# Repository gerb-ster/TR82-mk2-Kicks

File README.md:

# TR82 mk2 'Kicks'

Second version of the TR82 project; proper PCB's this time! I've combined the BassDrums and the SnareDrum to 
a single board. I've added a OpAmp buffer to the output and changed the output impedance to a more standard
1k. Next to that I've also added a Gate-to-Trigger circuit based on a design by Ken Stone. It converts the 
rising edge of a Gate signal into a short trigger pulse. By changin the level of the gate/trigger input you
can control how 'hard' you hit the drums. Higher levels means more 'accent'.

The Designs and Mods of the drum voices are the same as in the 'original' TR82.

There is a 'internal trigger' connection added to the mainboard of the PCB. This can be used to hook it up to
a seperate controller board. Maybe :). 

### Links

https://www.gerbster.nl/tr82/  
https://www.elby-designs.com/webtek/cgs/cgs24/cgs24_gatetotrigger.html

## Status: Work in Progress

- done: first schematic & board design
- done: breadboard and test
- done: design frontpanel
- todo: order PCB and build prototype

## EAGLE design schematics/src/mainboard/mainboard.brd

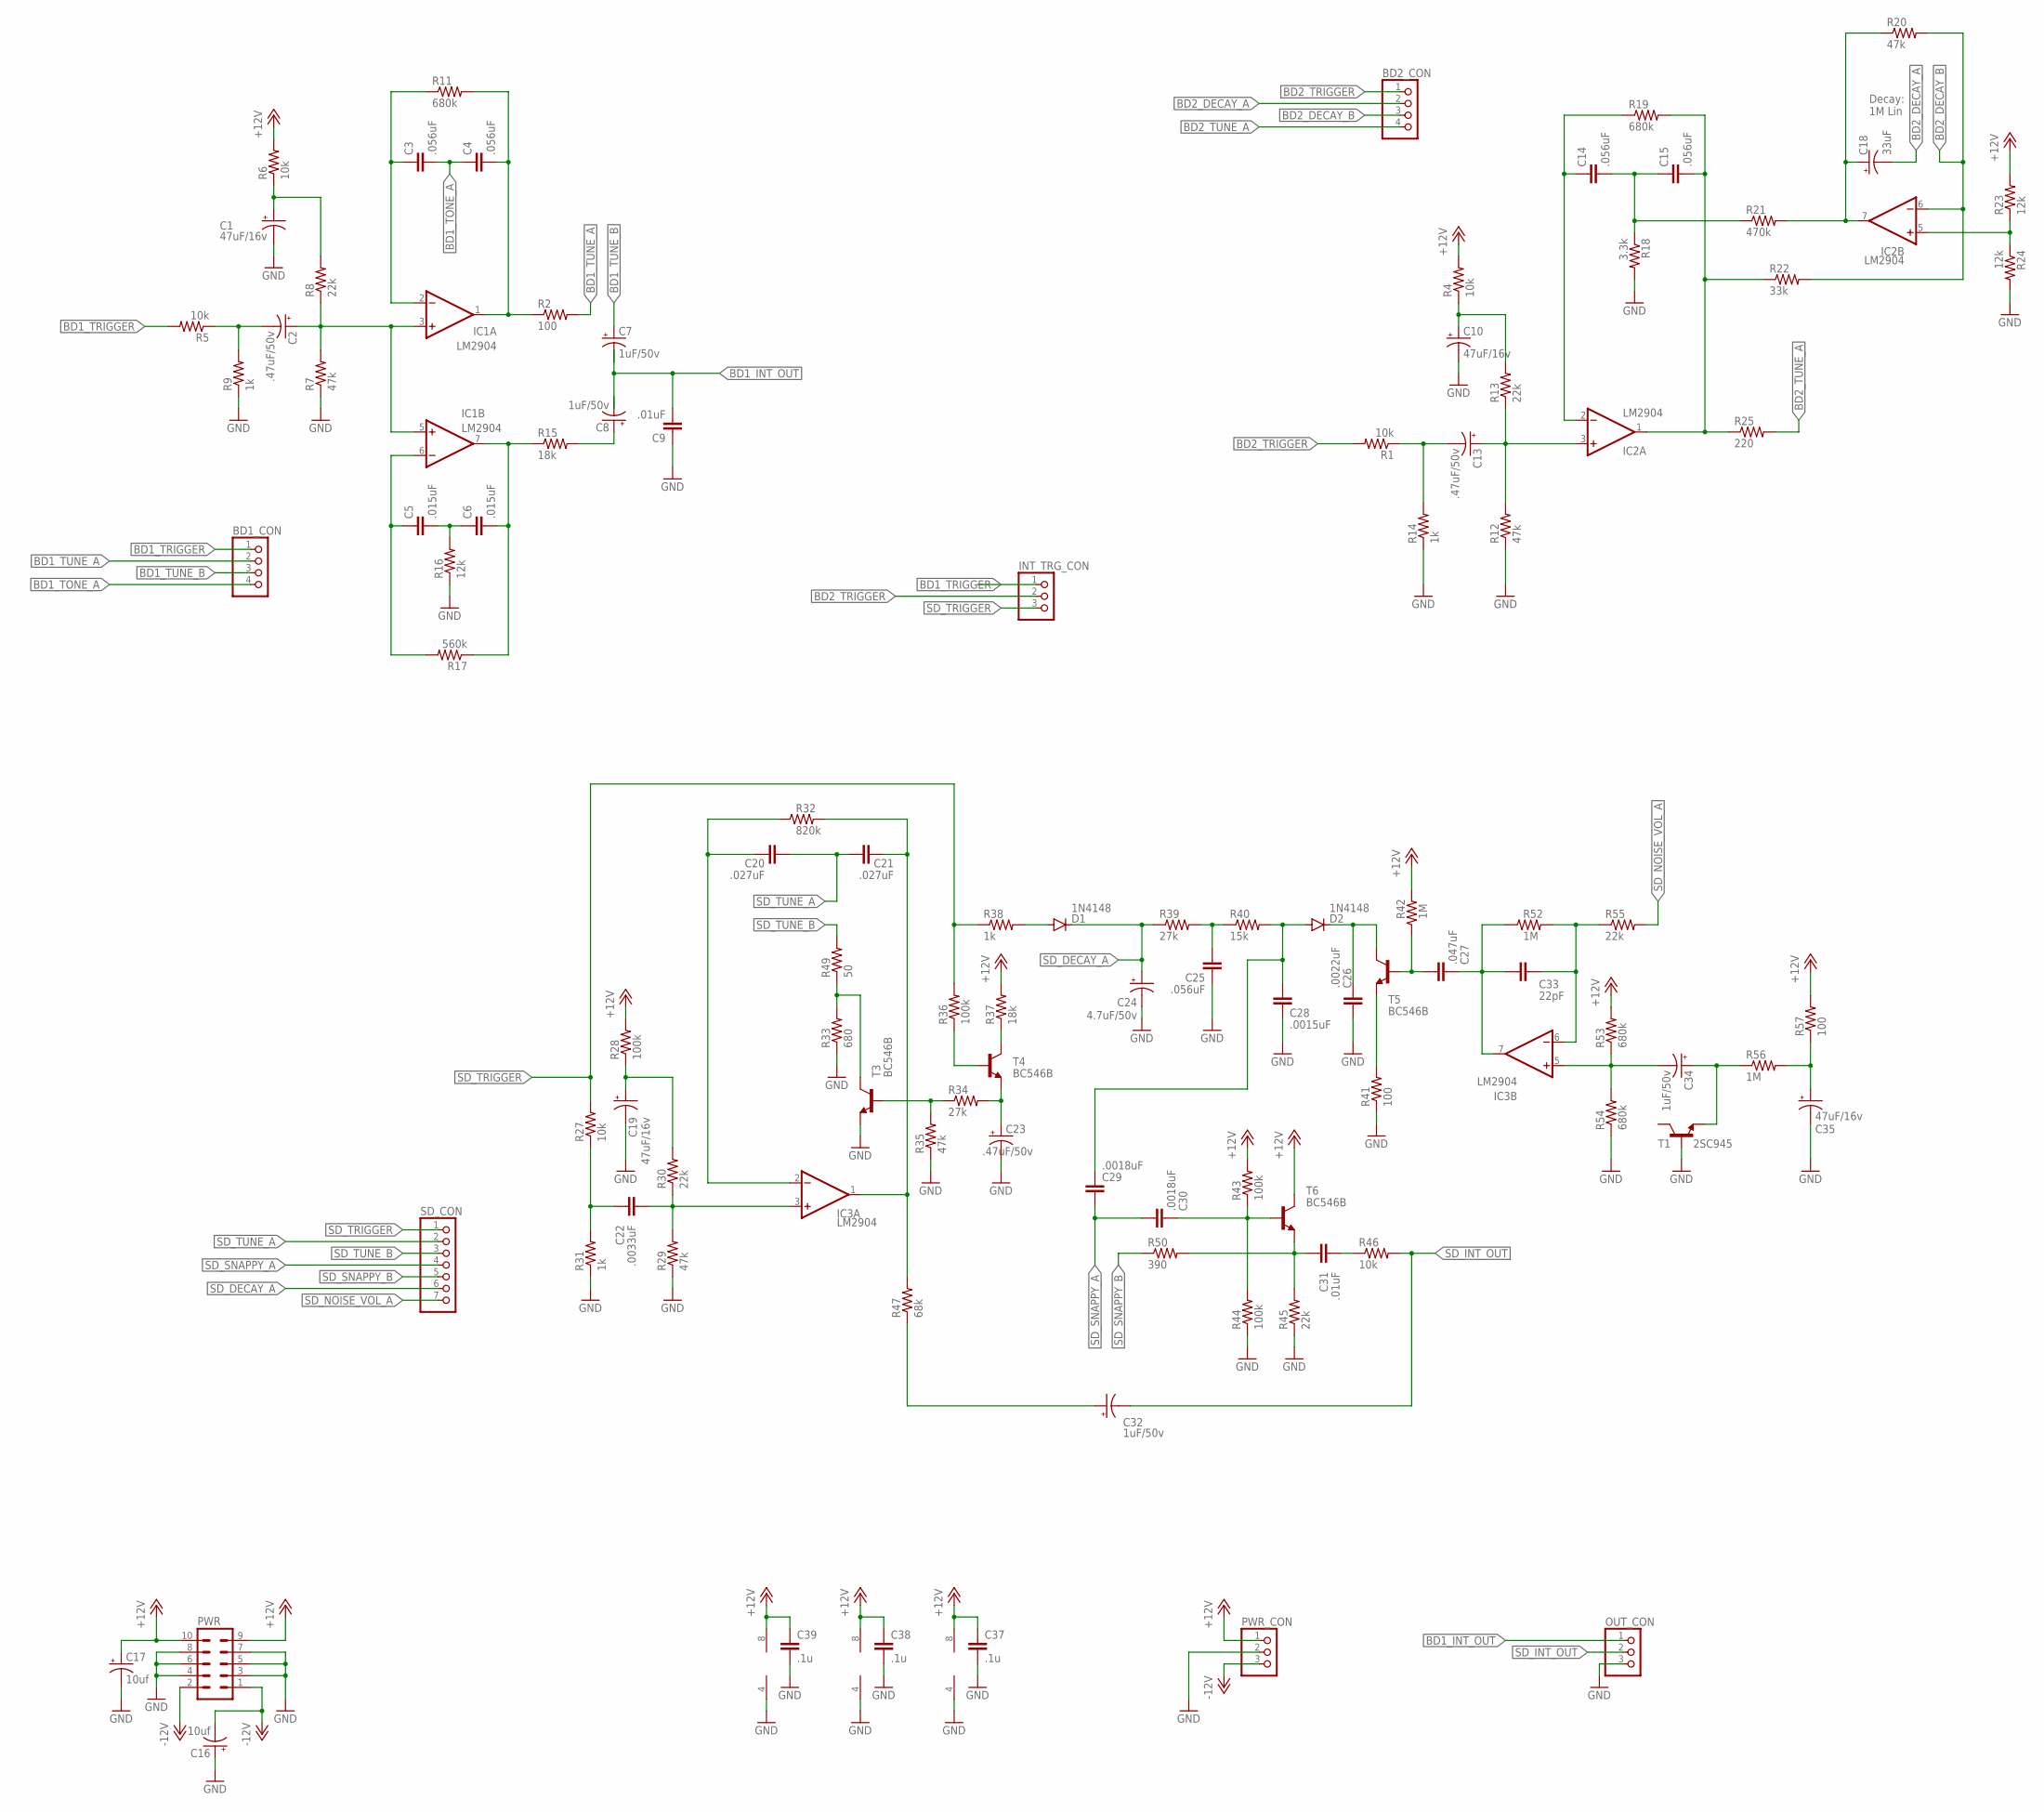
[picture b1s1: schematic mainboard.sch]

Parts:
BD1_CON, BD2_CON: PINHD-1X4; 1X04
C1, C35: 47uF/16v; E2,5-5
C2: .47uF/50v; E2,5-5
C3, C4, C14, C15, C25: .056uF; C050-024X044
C5, C6: .015uF; C050-024X044
C7, C8, C34: 1uF/50v; E2,5-5
C9, C31: .01uF; C050-024X044
C10, C19: 47uF/16v; E2,5-6
C13, C23: .47uF/50v; E2,5-6
C16, C17: 10uf; E2,5-5
C18: 33uF; E2,5-5
C20, C21: .027uF; C050-024X044
C22: .0033uF; C050-024X044
C24: 4.7uF/50v; E2,5-6
C26: .0022uF; C050-024X044
C27: .047uF; C050-024X044
C28: .0015uF; C050-024X044
C29, C30: .0018uF; C050-024X044
C32: 1uF/50v; E2,5-6
C33: 22pF; C050-024X044
C37, C38, C39: .1u; C050-024X044
D1, D2: 1N4148; DO35-7
IC1, IC2, IC3: LM2904; DIL08
INT_TRG_CON: PINHD-1X3; 1X03
OUT_CON: PINHD-1X3; 1X03
PWR: ML10
PWR_CON: PINHD-1X3; 1X03
R1, R4, R5, R6, R27, R46: 10k; 0207/7
R2, R41, R57: 100; 0207/7
R7, R12, R20, R29, R35: 47k; 0207/7
R8, R13, R30, R45, R55: 22k; 0207/7
R9, R14, R31, R38: 1k; 0207/7
R11, R19, R53, R54: 680k; 0207/7
R15, R37: 18k; 0207/7
R16, R23, R24: 12k; 0207/7
R17: 560k; 0207/7
R18: 3.3k; 0207/7
R21: 470k; 0207/7
R22: 33k; 0207/7
R25: 220; 0207/7
R28, R36, R43, R44: 100k; 0207/7
R32: 820k; 0207/2V
R33: 680; 0207/7
R34, R39: 27k; 0207/7
R40: 15k; 0207/7
R42, R52, R56: 1M; 0207/7
R47: 68k; 0207/7
R49: 50; 0207/7
R50: 390; 0207/7
SD_CON: PINHD-1X7; 1X07
T1: 2SC945; TO92-ECB
T3, T4, T5, T6: BC546B; TO92-CBE

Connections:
+12V: C17.+, C37.1, C38.1, C39.1, IC1.8 (V+), IC2.8 (V+), IC3.8 (V+), PWR.9, PWR.10, PWR_CON.1, R4.2, R6.2, R23.2, R28.2, R37.2, R42.2, R43.2, R53.2, R57.2, T6.C
-12V: C16.-, PWR.1, PWR.2, PWR_CON.3
BD1_INT_OUT: C7.-, C8.-, C9.2, OUT_CON.1
BD1_TONE_A: BD1_CON.4, C3.2, C4.1
BD1_TRIGGER: BD1_CON.1, INT_TRG_CON.1, R5.2
BD1_TUNE_A: BD1_CON.2, R2.2
BD1_TUNE_B: BD1_CON.3, C7.+
BD2_DECAY_A: BD2_CON.2, C18.-
BD2_DECAY_B: BD2_CON.3, IC2.6 (-IN), R20.2, R22.2
BD2_TRIGGER: BD2_CON.1, INT_TRG_CON.2, R1.2
BD2_TUNE_A: BD2_CON.4, R25.2
GND: C1.-, C9.1, C10.-, C16.+, C17.-, C19.-, C23.-, C24.-, C25.1, C26.1, C28.1, C35.-, C37.2, C38.2, C39.2, IC1.4 (V-), IC2.4 (V-), IC3.4 (V-), OUT_CON.3, PWR.3, PWR.4, PWR.5, PWR.6, PWR.7, PWR.8, PWR_CON.2, R7.1, R9.1, R12.1, R14.1, R16.1, R18.2, R24.2, R29.1, R31.1, R33.1, R35.1, R41.1, R44.1, R45.1, R54.1, T1.B, T3.E
unnamed: C13.-, R1.1, R14.2
unnamed: C2.-, R5.1, R9.2
unnamed: C2.+, IC1.3 (+IN), IC1.5 (+IN), R7.2, R8.1
unnamed: C1.+, R6.1, R8.2
unnamed: C5.2, C6.1, R16.2
unnamed: C3.1, IC1.2 (-IN), R11.1
unnamed: C13.+, IC2.3 (+IN), R12.2, R13.1
unnamed: C10.+, R4.1, R13.2
unnamed: C6.2, IC1.7 (OUT), R15.1, R17.1
unnamed: C5.1, IC1.6 (-IN), R17.2
unnamed: C4.2, IC1.1 (OUT), R2.1, R11.2
unnamed: C8.+, R15.2
unnamed: C14.1, IC2.2 (-IN), R19.1
unnamed: C14.2, C15.1, R18.1, R21.1
unnamed: C15.2, IC2.1 (OUT), R19.2, R22.1, R25.1
unnamed: C18.+, IC2.7 (OUT), R20.1, R21.2
unnamed: IC2.5 (+IN), R23.1, R24.1
unnamed: C22.1, R27.1, R31.2
unnamed: C22.2, IC3.3 (+IN), R29.2, R30.1
unnamed: C19.+, R28.1, R30.2
unnamed: C20.1, IC3.2 (-IN), R32.1
unnamed: C21.2, IC3.1 (OUT), R32.2, R47.2
unnamed: R33.2, R49.1, T3.C
unnamed: R34.1, R35.2, T3.B
unnamed: C23.+, R34.2, T4.E
unnamed: R36.1, T4.B
unnamed: R37.1, T4.C
unnamed: D1.A, R38.2
unnamed: C25.2, R39.2, R40.1
unnamed: C28.2, C29.1, D2.A, R40.2
unnamed: C26.2, D2.C, T5.C
unnamed: R41.2, T5.E
unnamed: C27.1, R42.1, T5.B
unnamed: C31.1, R45.2, R50.2, T6.E
unnamed: C31.2, R46.1
unnamed: C32.+, R47.1
unnamed: C30.2, R43.1, R44.2, T6.B
unnamed: C27.2, C33.1, IC3.7 (OUT), R52.1
unnamed: C33.2, IC3.6 (-IN), R52.2, R55.1
unnamed: C34.-, IC3.5 (+IN), R53.1, R54.2
unnamed: C34.+, R56.1, T1.E
unnamed: C35.+, R56.2, R57.1
SD_DECAY_A: C24.+, D1.C, R39.1, SD_CON.6
SD_INT_OUT: C32.-, OUT_CON.2, R46.2
SD_NOISE_VOL_A: R55.2, SD_CON.7
SD_SNAPPY_A: C29.2, C30.1, SD_CON.4
SD_SNAPPY_B: R50.1, SD_CON.5
SD_TRIGGER: INT_TRG_CON.3, R27.2, R36.2, R38.1, SD_CON.1
SD_TUNE_A: C20.2, C21.1, SD_CON.2
SD_TUNE_B: R49.2, SD_CON.3

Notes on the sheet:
Decay: 1M Lin

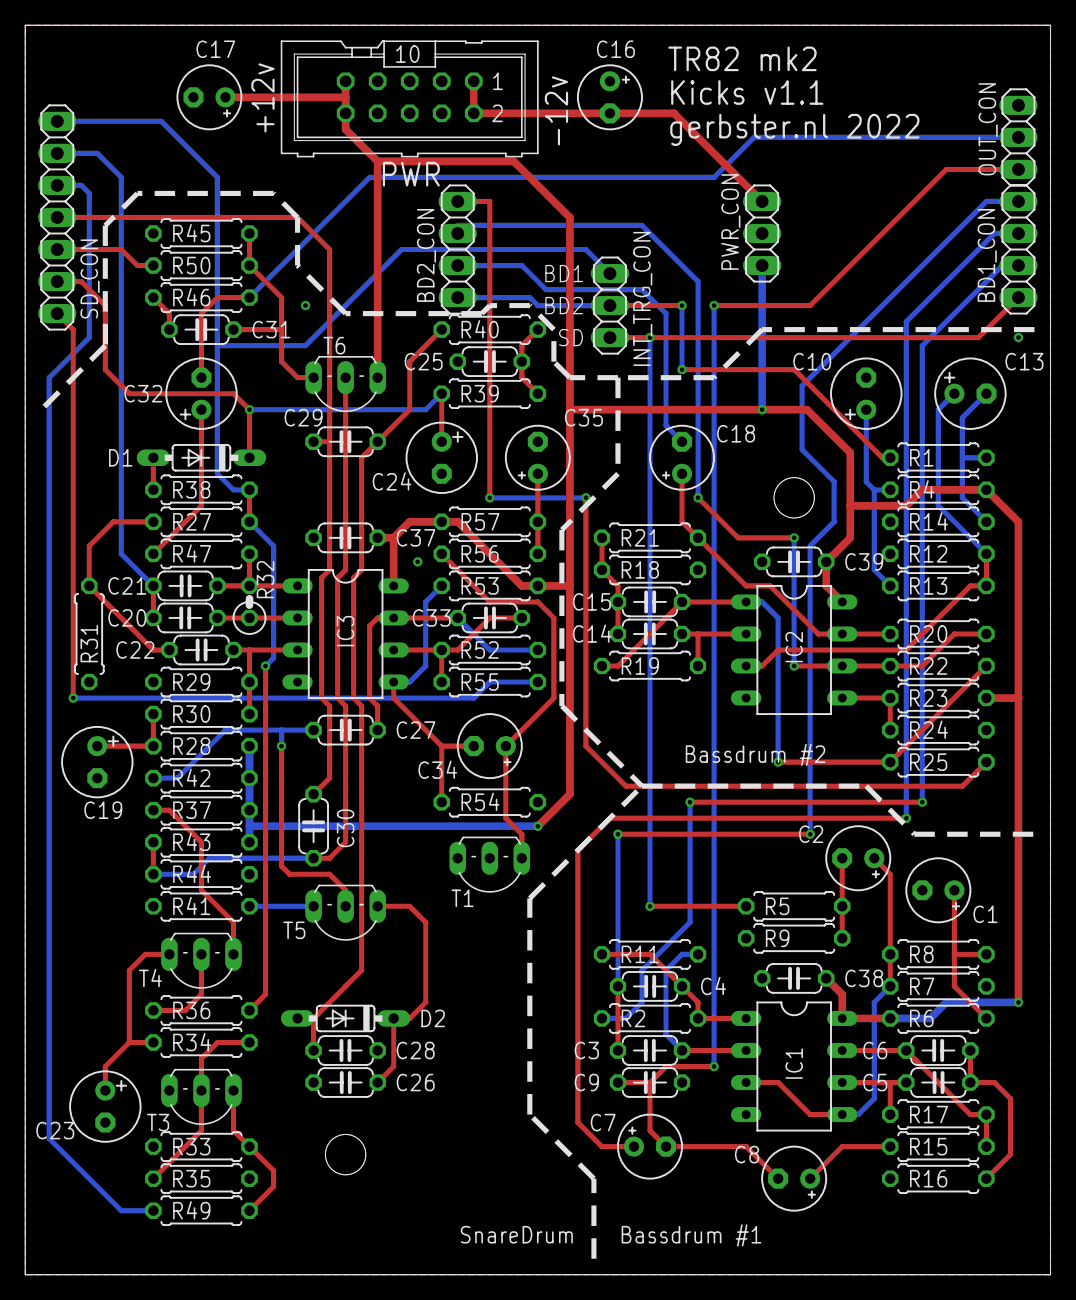
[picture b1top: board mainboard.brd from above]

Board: 2 copper layers, 81.3 x 99.1 mm, 105 parts (0 on the bottom side), 62 nets.

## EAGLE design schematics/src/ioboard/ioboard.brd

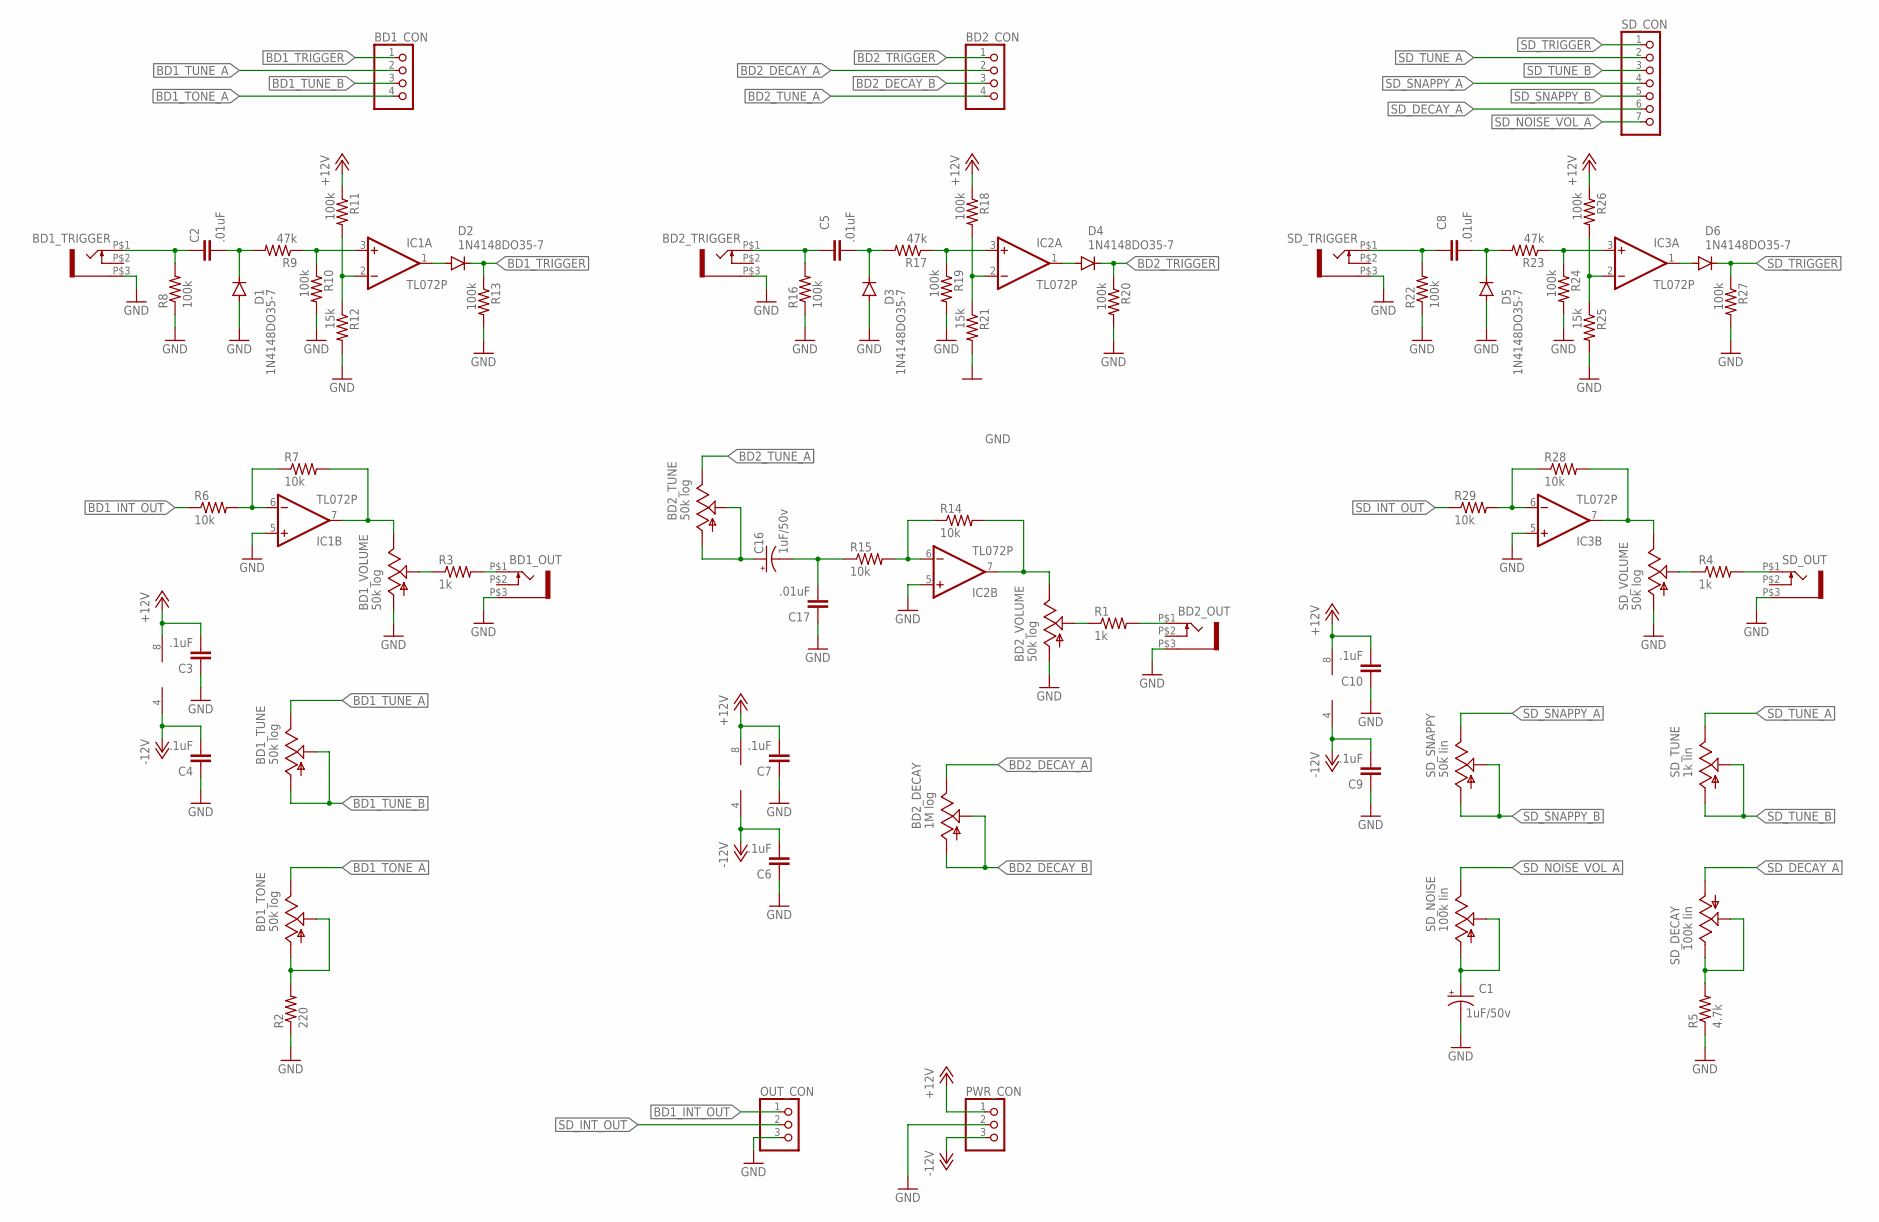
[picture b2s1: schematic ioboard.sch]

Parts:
BD1_CON, BD2_CON: PINHD-1X4; 1X04
BD1_OUT, BD1_TRIGGER, BD2_OUT, BD2_TRIGGER: WQP-PJ301M-12_JACK
BD1_TONE, BD1_TUNE, BD1_VOLUME, BD2_TUNE, BD2_VOLUME: 50k log; EVUF
BD2_DECAY: 1M log; EVUF
C1: 1uF/50v; E2,5-5
C2, C5, C8, C17: .01uF; C050-024X044
C3, C4, C6, C7, C9, C10: .1uF; C050-024X044
C16: 1uF/50v; E2,5-6
D1, D2, D3, D4, D5, D6: 1N4148DO35-7; DO35-7
IC1, IC2, IC3: TL072P; DIL08
OUT_CON: PINHD-1X3; 1X03
PWR_CON: PINHD-1X3; 1X03
R1, R3, R4: 1k; 0207/7
R2: 220; 0207/7
R5: 4.7k; 0207/7
R6, R7, R14, R15, R28, R29: 10k; 0207/7
R8, R10, R11, R13, R16, R18, R19, R20, R22, R24, R26, R27: 100k; 0207/7
R9, R17, R23: 47k; 0207/7
R12, R21, R25: 15k; 0207/7
SD_CON: PINHD-1X7; 1X07
SD_DECAY: 100k lin; EVUF
SD_NOISE: 100k lin; EVUF
SD_OUT: WQP-PJ301M-12_JACK
SD_SNAPPY: 50k lin; EVUF
SD_TRIGGER: WQP-PJ301M-12_JACK
SD_TUNE: 1k lin; EVUF
SD_VOLUME: 50k log; EVUF

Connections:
+12V: C3.2, C7.2, C10.2, IC1.8 (V+), IC2.8 (V+), IC3.8 (V+), PWR_CON.1, R11.1, R18.1, R26.1
-12V: C4.2, C6.2, C9.2, IC1.4 (V-), IC2.4 (V-), IC3.4 (V-), PWR_CON.3
BD1_INT_OUT: OUT_CON.1, R6.1
BD1_OUT: BD1_OUT.P$1 (2), R3.2
BD1_TONE_A: BD1_CON.4, BD1_TONE.3 (E)
BD1_TONE_B: BD1_TONE.1 (A), BD1_TONE.2 (S), R2.2
BD1_TRIGGER: BD1_CON.1, D2.C, R13.1
BD1_TUNE_A: BD1_CON.2, BD1_TUNE.3 (E)
BD1_TUNE_B: BD1_CON.3, BD1_TUNE.1 (A), BD1_TUNE.2 (S)
BD2_DECAY_A: BD2_CON.2, BD2_DECAY.3 (E)
BD2_DECAY_B: BD2_CON.3, BD2_DECAY.1 (A), BD2_DECAY.2 (S)
BD2_INT_OUT: C16.-, C17.2, R15.1
BD2_TRIGGER: BD2_CON.1, D4.C, R20.1
BD2_TUNE_A: BD2_CON.4, BD2_TUNE.3 (E)
BD2_TUNE_B: BD2_TUNE.1 (A), BD2_TUNE.2 (S), C16.+
GND: BD1_OUT.P$3 (1), BD1_TRIGGER.P$3 (1), BD1_VOLUME.1 (A), BD2_OUT.P$3 (1), BD2_TRIGGER.P$3 (1), BD2_VOLUME.1 (A), C1.-, C3.1, C4.1, C6.1, C7.1, C9.1, C10.1, C17.1, D1.A, D3.A, D5.A, IC1.5 (+IN), IC2.5 (+IN), IC3.5 (+IN), OUT_CON.3, PWR_CON.2, R2.1, R5.1, R8.1, R10.2, R12.2, R13.2, R16.1, R19.2, R20.2, R21.2, R22.1, R24.2, R25.2, R27.2, SD_OUT.P$3 (1), SD_TRIGGER.P$3 (1), SD_VOLUME.1 (A)
unnamed: BD1_VOLUME.2 (S), R3.1
unnamed: R4.1, SD_VOLUME.2 (S)
unnamed: BD2_OUT.P$1 (2), R1.2
unnamed: BD2_VOLUME.2 (S), R1.1
unnamed: R4.2, SD_OUT.P$1 (2)
unnamed: IC1.6 (-IN), R6.2, R7.1
unnamed: R5.2, SD_DECAY.2 (S), SD_DECAY.3 (E)
unnamed: BD1_TRIGGER.P$1 (2), C2.1, R8.2
unnamed: C2.2, D1.C, R9.2
unnamed: IC1.3 (+IN), R9.1, R10.1
unnamed: IC1.2 (-IN), R11.2, R12.1
unnamed: D2.A, IC1.1 (OUT)
unnamed: BD2_VOLUME.3 (E), IC2.7 (OUT), R14.2
unnamed: IC2.6 (-IN), R14.1, R15.2
unnamed: BD2_TRIGGER.P$1 (2), C5.1, R16.2
unnamed: C5.2, D3.C, R17.2
unnamed: IC2.3 (+IN), R17.1, R19.1
unnamed: D4.A, IC2.1 (OUT)
unnamed: IC3.6 (-IN), R28.1, R29.2
unnamed: IC2.2 (-IN), R18.2, R21.1
unnamed: C8.1, R22.2, SD_TRIGGER.P$1 (2)
unnamed: C8.2, D5.C, R23.2
unnamed: IC3.3 (+IN), R23.1, R24.1
unnamed: IC3.2 (-IN), R25.1, R26.2
unnamed: D6.A, IC3.1 (OUT)
unnamed: IC3.7 (OUT), R28.2, SD_VOLUME.3 (E)
unnamed: BD1_VOLUME.3 (E), IC1.7 (OUT), R7.2
SD_DECAY_A: SD_CON.6, SD_DECAY.1 (A)
SD_INT_OUT: OUT_CON.2, R29.1
SD_NOISE_B: C1.+, SD_NOISE.1 (A), SD_NOISE.2 (S)
SD_NOISE_VOL_A: SD_CON.7, SD_NOISE.3 (E)
SD_SNAPPY_A: SD_CON.4, SD_SNAPPY.3 (E)
SD_SNAPPY_B: SD_CON.5, SD_SNAPPY.1 (A), SD_SNAPPY.2 (S)
SD_TRIGGER: D6.C, R27.1, SD_CON.1
SD_TUNE_A: SD_CON.2, SD_TUNE.3 (E)
SD_TUNE_B: SD_CON.3, SD_TUNE.1 (A), SD_TUNE.2 (S)

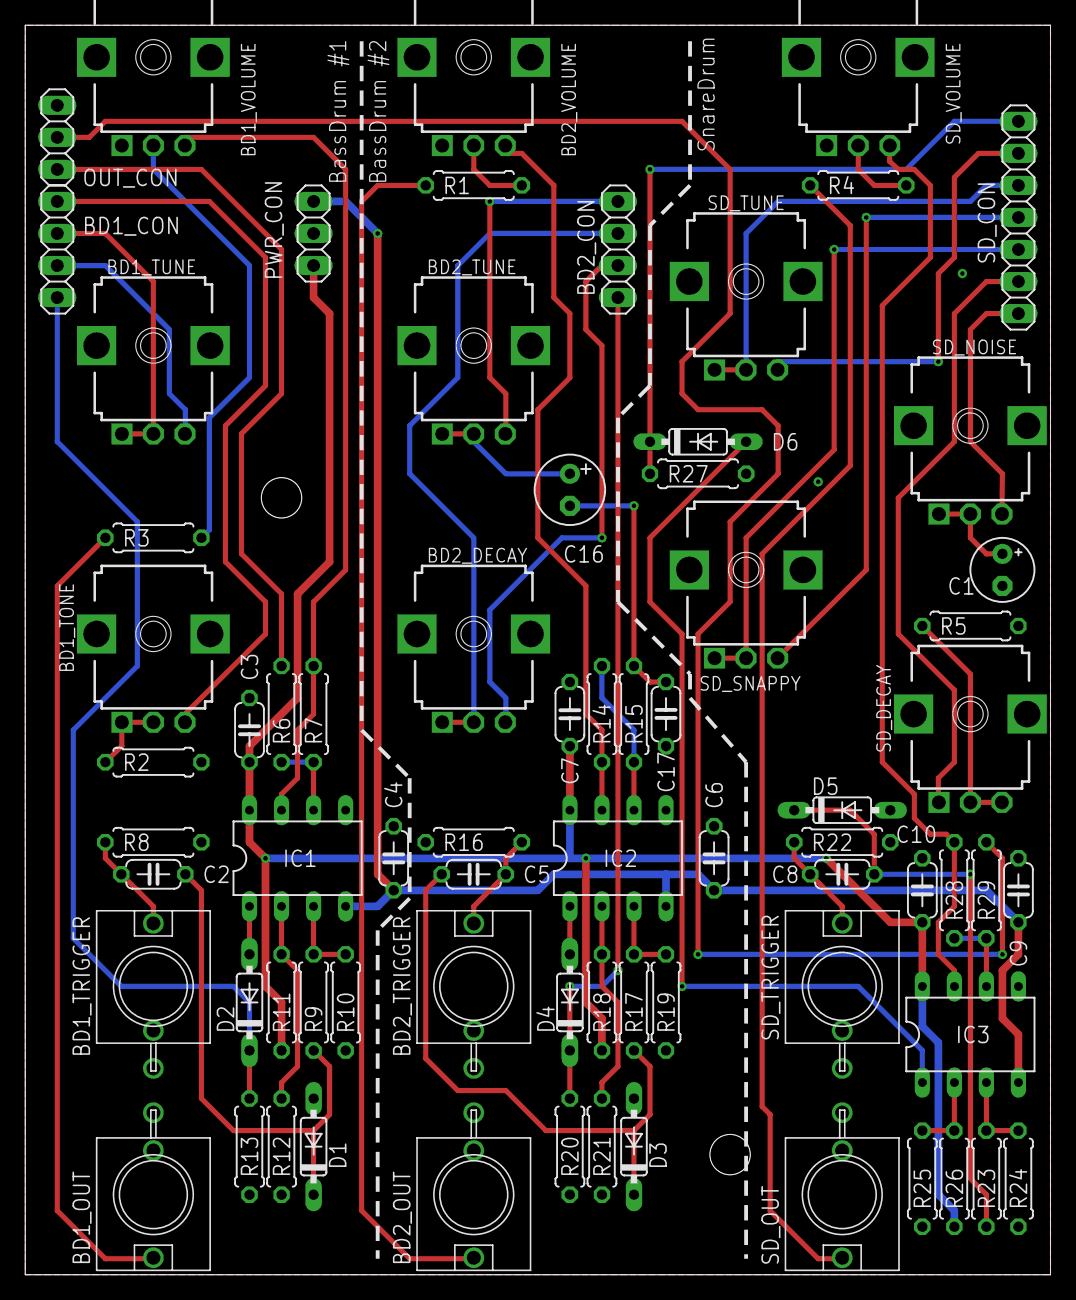
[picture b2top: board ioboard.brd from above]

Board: 2 copper layers, 81.3 x 99.1 mm, 72 parts (0 on the bottom side), 52 nets.

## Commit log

2021-05-18 Added Faceplates
2021-05-18 Added faceplate design setup
2021-05-19 Updated Schematics & Readme
2021-06-07 Updated Schematics & Firmware
2021-06-15 Updated Schematics, Fixed Power Socket orientation
2021-07-19 Fixed minor issues, added documentation and updated some faceplates
2021-08-06 Updated some schematics and docs
2021-08-10 Fixed some bugs and updated documentation
2022-04-20 Some updates & bugfixes
2022-04-22 Fixed schematics & descriptions
2022-05-17 Updated Firmware
2022-05-18 Updated Faceplates
2022-05-18 Fixed issues
2022-05-21 Fixed schematics
2022-05-28 General updates
2022-06-02 Fixed orentation SD Decay pot
2022-06-13 Updated FacePlate designs
